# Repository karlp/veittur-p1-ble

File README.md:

## P1 HAN port to BLE

Nothing fancy, a euro HAN P1 port from an electricity meter to BLE.
Includes a ws2812 style LED for local indication, and a header for debug and programming.
Nothing else at all really, total BOM is ~$2.  You'll need to add your own RJ12/6P6C cable,
and have BLE range.

intention is to re-use something that already exists in homeassistant protocol wise...

## Sample
### 2022-10 revision
Adds USB, parts replaced to match JLCPCB production.

### Initial revision (conflicting pin definitions, overly simplistic)

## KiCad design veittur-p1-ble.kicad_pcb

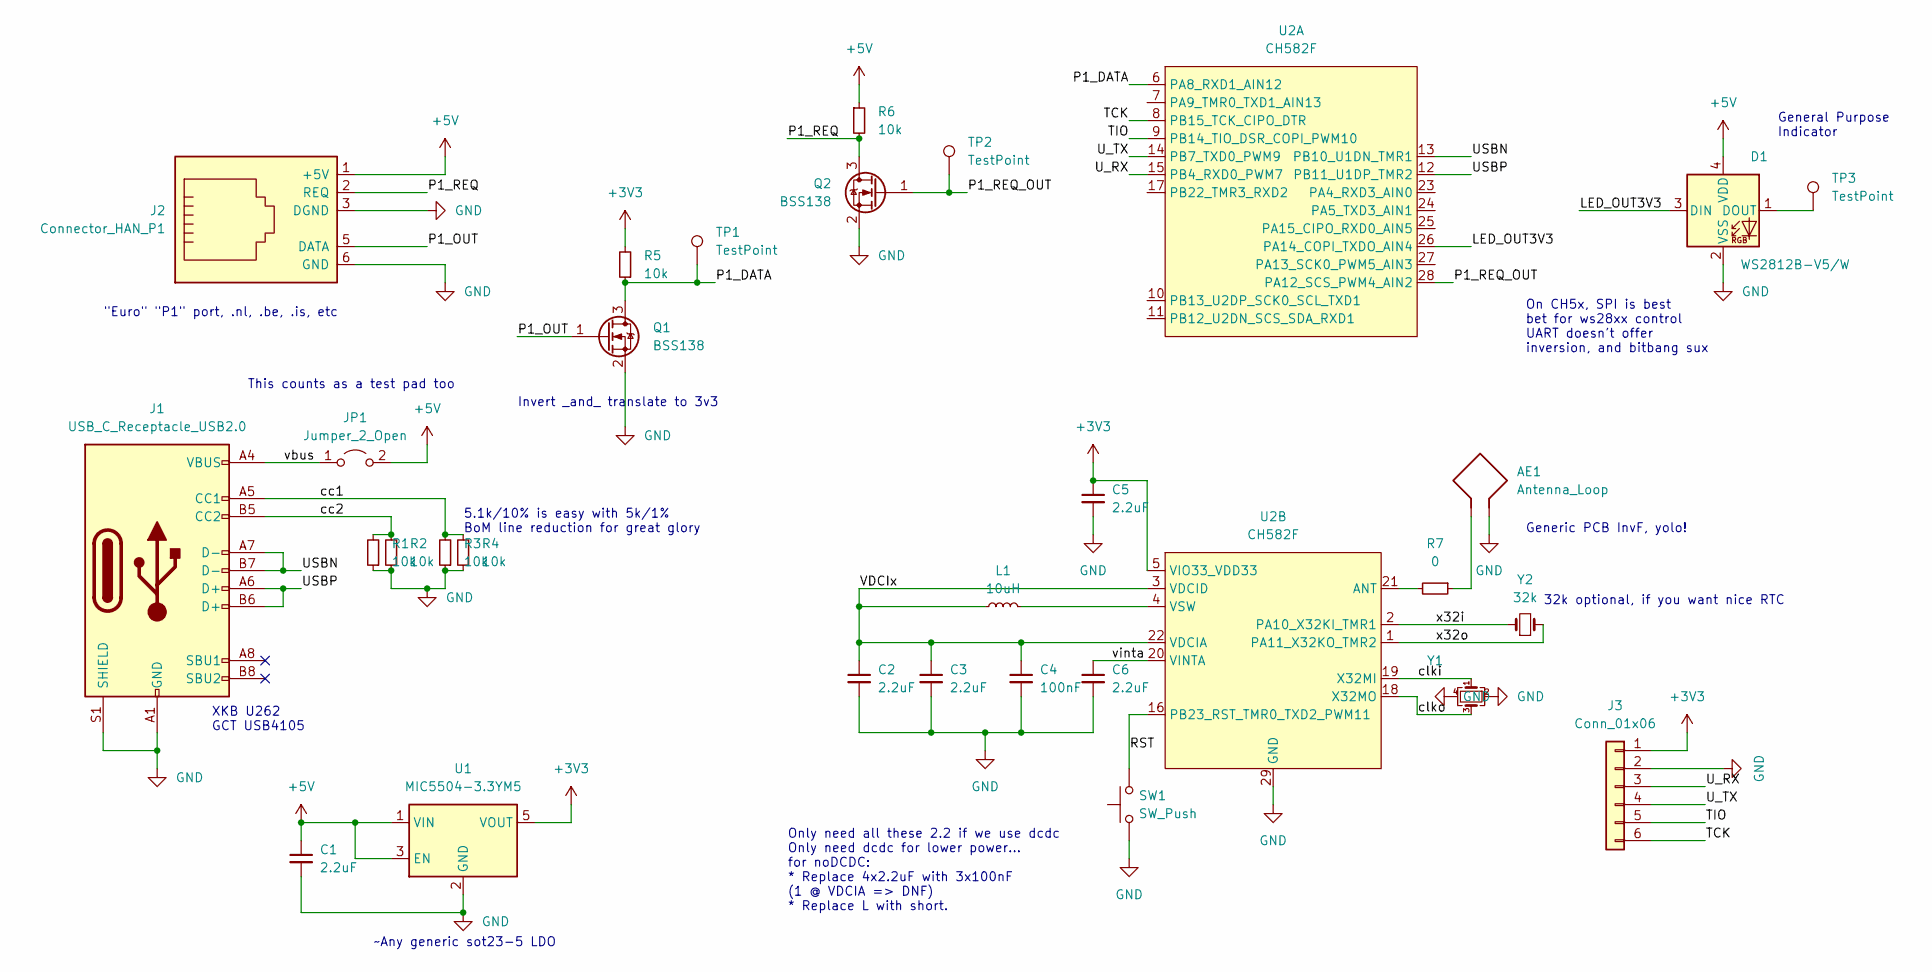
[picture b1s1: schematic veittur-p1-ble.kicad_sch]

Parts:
AE1: Antenna_Loop; ANT-F-1-2.4G-1.6MM-FR4-WCH-FLIP
C1, C2, C3, C5, C6: 2.2uF; C_0603_1608Metric; MPN CL10A225KO8NNNC; lcsc# C23630
C4: 100nF; C_0603_1608Metric; MPN CC0603KRX7R9BB104; lcsc# C14663
D1: WS2812B-V5/W; LED_WS2812B_PLCC4_5.0x5.0mm_P3.2mm; MPN WS2812B-V5/W; lcsc# C2874885
J1: USB_C_Receptacle_USB2.0; USB_C_Receptacle_XKB_U262-16XN-4BVC11; MPN U262-161N-4BVC11; lcsc# C319148
J2: Connector_HAN_P1; RJ25_Wayconn_MJEA-660X1_Horizontal; MPN R-RJ11R06P-A801
J3: Conn_01x06; PinHeader_1x06_P2.54mm_Vertical
JP1: Jumper_2_Open; PinHeader_2x01_P2.54mm_Vertical
L1: 10uH; L_Changjiang_FNR252012S; MPN SWPA252012S100MT; lcsc# C37428
Q1, Q2: BSS138; SOT-23; MPN AP2302B; lcsc# C406812
R1, R2, R3, R4, R5, R6: 10k; R_0603_1608Metric; MPN 0603WAF1002T5E; lcsc# C25804
R7: 0; R_0603_1608Metric; MPN 0603WAF0000T5E; lcsc# C21189
SW1: SW_Push; PinHeader_2x01_P1.27mm_Vertical
TP1, TP2, TP3: TestPoint; TestPoint_Plated_Hole_0.6_D0.8mm
U1: MIC5504-3.3YM5; SOT-23-5; MPN XC6219B332MR; lcsc# C347386
U2: CH582F; QFN-28-1EP_4x4mm_P0.4mm_EP2.6x2.6mm; MPN CH582F; lcsc# C3001175
Y1: 32M; Crystal_SMD_3225-4Pin_3.2x2.5mm; MPN X322532MMB4SI; lcsc# C337683
Y2: 32k; Crystal_SMD_3215-2Pin_3.2x1.5mm; MPN Q13FC1350000400; lcsc# C271654

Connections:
+3V3: C5.1, J3.1, R5.2, U1.5 (VOUT), U2.5 (VIO33_VDD33)
+5V: C1.1, D1.4 (VDD), J2.1 (+5V), JP1.2 (B), R6.1, U1.1 (VIN), U1.3 (EN)
/LED_OUT3V3: D1.3 (DIN), U2.26 (PA14_COPI_TXDO_AIN4)
/P1_DATA: Q1.3 (D), R5.1, TP1.1, U2.6 (PA8_RXD1_AIN12)
/P1_OUT: J2.5 (DATA), Q1.1 (G)
/P1_REQ: J2.2 (REQ), Q2.3 (D), R6.2
/P1_REQ_OUT: Q2.1 (G), TP2.1, U2.28 (PA12_SCS_PWM4_AIN2)
/RST: SW1.2, U2.16 (PB23_RST_TMR0_TXD2_PWM11)
/TCK: J3.6, U2.8 (PB15_TCK_CIPO_DTR)
/TIO: J3.5, U2.9 (PB14_TIO_DSR_COPI_PWM10)
/USBN: J1.A7 (D-), J1.B7 (D-), U2.13 (PB10_U1DN_TMR1)
/USBP: J1.A6 (D+), J1.B6 (D+), U2.12 (PB11_U1DP_TMR2)
/U_RX: J3.3, U2.15 (PB4_RXD0_PWM7)
/U_TX: J3.4, U2.14 (PB7_TXD0_PWM9)
/VDCIx: C2.1, C3.1, C4.1, L1.1, U2.3 (VDCID), U2.22 (VDCIA)
/cc1: J1.A5 (CC1), R3.2, R4.2
/cc2: J1.B5 (CC2), R1.2, R2.2
/clki: U2.19 (X32MI), Y1.1
/clko: U2.18 (X32MO), Y1.3
/vbus: J1.A4 (VBUS), J1.A9 (VBUS), J1.B4 (VBUS), J1.B9 (VBUS), JP1.1 (A)
/vinta: C6.1, U2.20 (VINTA)
/x32i: U2.2 (PA10_X32KI_TMR1), Y2.1
/x32o: U2.1 (PA11_X32KO_TMR2), Y2.2
GND: AE1.2, C1.2, C2.2, C3.2, C4.2, C5.2, C6.2, D1.2 (VSS), J1.A1 (GND), J1.A12 (GND), J1.B1 (GND), J1.B12 (GND), J1.S1 (SHIELD), J2.3 (DGND), J2.6 (GND), J3.2, Q1.2 (S), Q2.2 (S), R1.1, R2.1, R3.1, R4.1, SW1.1, U1.2 (GND), U2.29 (GND), Y1.2, Y1.4
unnamed: AE1.1, R7.1
unnamed: D1.1 (DOUT), TP3.1
unnamed: L1.2, U2.4 (VSW)
unnamed: R7.2, U2.21 (ANT)

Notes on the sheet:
32k optional, if you want nice RTC
Invert _and_ translate to 3v3
~Any generic sot23-5 LDO
This counts as a test pad too
5.1k/10% is easy with 5k/1% BoM line reduction for great glory
"Euro" "P1" port, .nl, .be, .is, etc
XKB U262 GCT USB4105
General Purpose Indicator
On CH5x, SPI is best bet for ws28xx control UART doesn't offer inversion, and bitbang sux
Only need all these 2.2 if we use dcdc Only need dcdc for lower power... for noDCDC: * Replace 4x2.2uF with 3x100nF (1 @ VDCIA => DNF) * Replace L with short.
Generic PCB InvF, yolo!

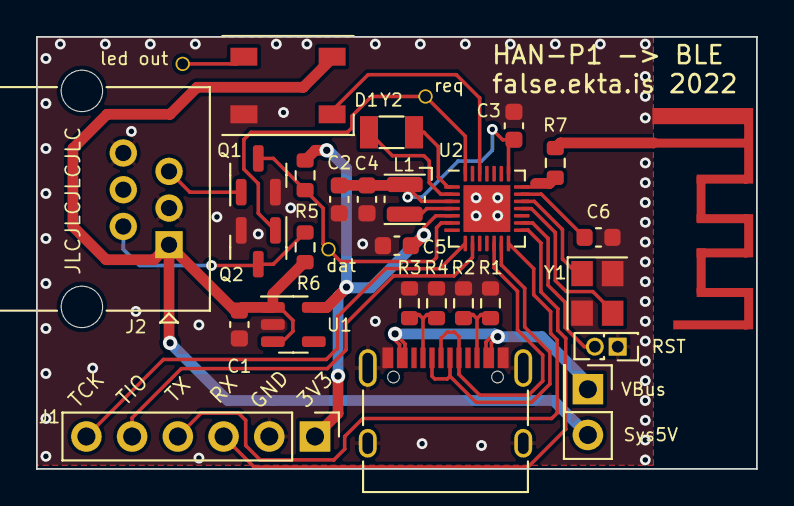
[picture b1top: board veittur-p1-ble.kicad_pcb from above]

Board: 2 copper layers, 40.0 x 24.0 mm, 30 parts (0 on the bottom side), 28 nets.

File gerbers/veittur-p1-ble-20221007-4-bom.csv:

Comment,Designator,Footprint,JLCPCB Part #
WS2812B-V5/W,D1,LED_WS2812B_PLCC4_5.0x5.0mm_P3.2mm,C2874885
10uH,L1,L_Changjiang_FNR252012S,C37428
BSS138,"Q1,Q2",SOT-23,C406812
MIC5504-3.3YM5,U1,SOT-23-5,C347386
2.2uF,"C2,C6,C5,C1,C3",C_0603_1608Metric,C23630
32M,Y1,Crystal_SMD_3225-4Pin_3.2x2.5mm,C337683
10k,"R3,R1,R4,R6,R2,R5",R_0603_1608Metric,C25804
0,R7,R_0603_1608Metric,C21189
CH582F,U2,QFN-28-1EP_4x4mm_P0.4mm_EP2.6x2.6mm,C3001175
32k,Y2,Crystal_SMD_3215-2Pin_3.2x1.5mm,C271654
USB_C_Receptacle_USB2.0,J1,USB_C_Receptacle_XKB_U262-16XN-4BVC11,C319148
100nF,C4,C_0603_1608Metric,C14663

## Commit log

2022-06-08 initial commit
    Antenna gnd return insn't connecting properly? what?
2022-06-08 initial "complete"
    is that it? should I just order this then?
2022-06-08 sample view
2022-06-08 add production gerbers
2022-09-06 add fixit notes for future revs
2022-09-06 sch: "fix" "most" fixmes...
    needs review and footprint assignments
2022-10-07 overhaul for jlc assembly
    parts changes, revised layout, added the usb connector, just for fun...
2022-10-07 finalize production for rev2.
    parts all adjusted for JLCPCB, bom and position files all uploaded
    happily.
2022-10-07 save more parts, always saves digging it all up again
2022-10-07 new board view image
2022-10-07 Generate new pdfs and set page settings
